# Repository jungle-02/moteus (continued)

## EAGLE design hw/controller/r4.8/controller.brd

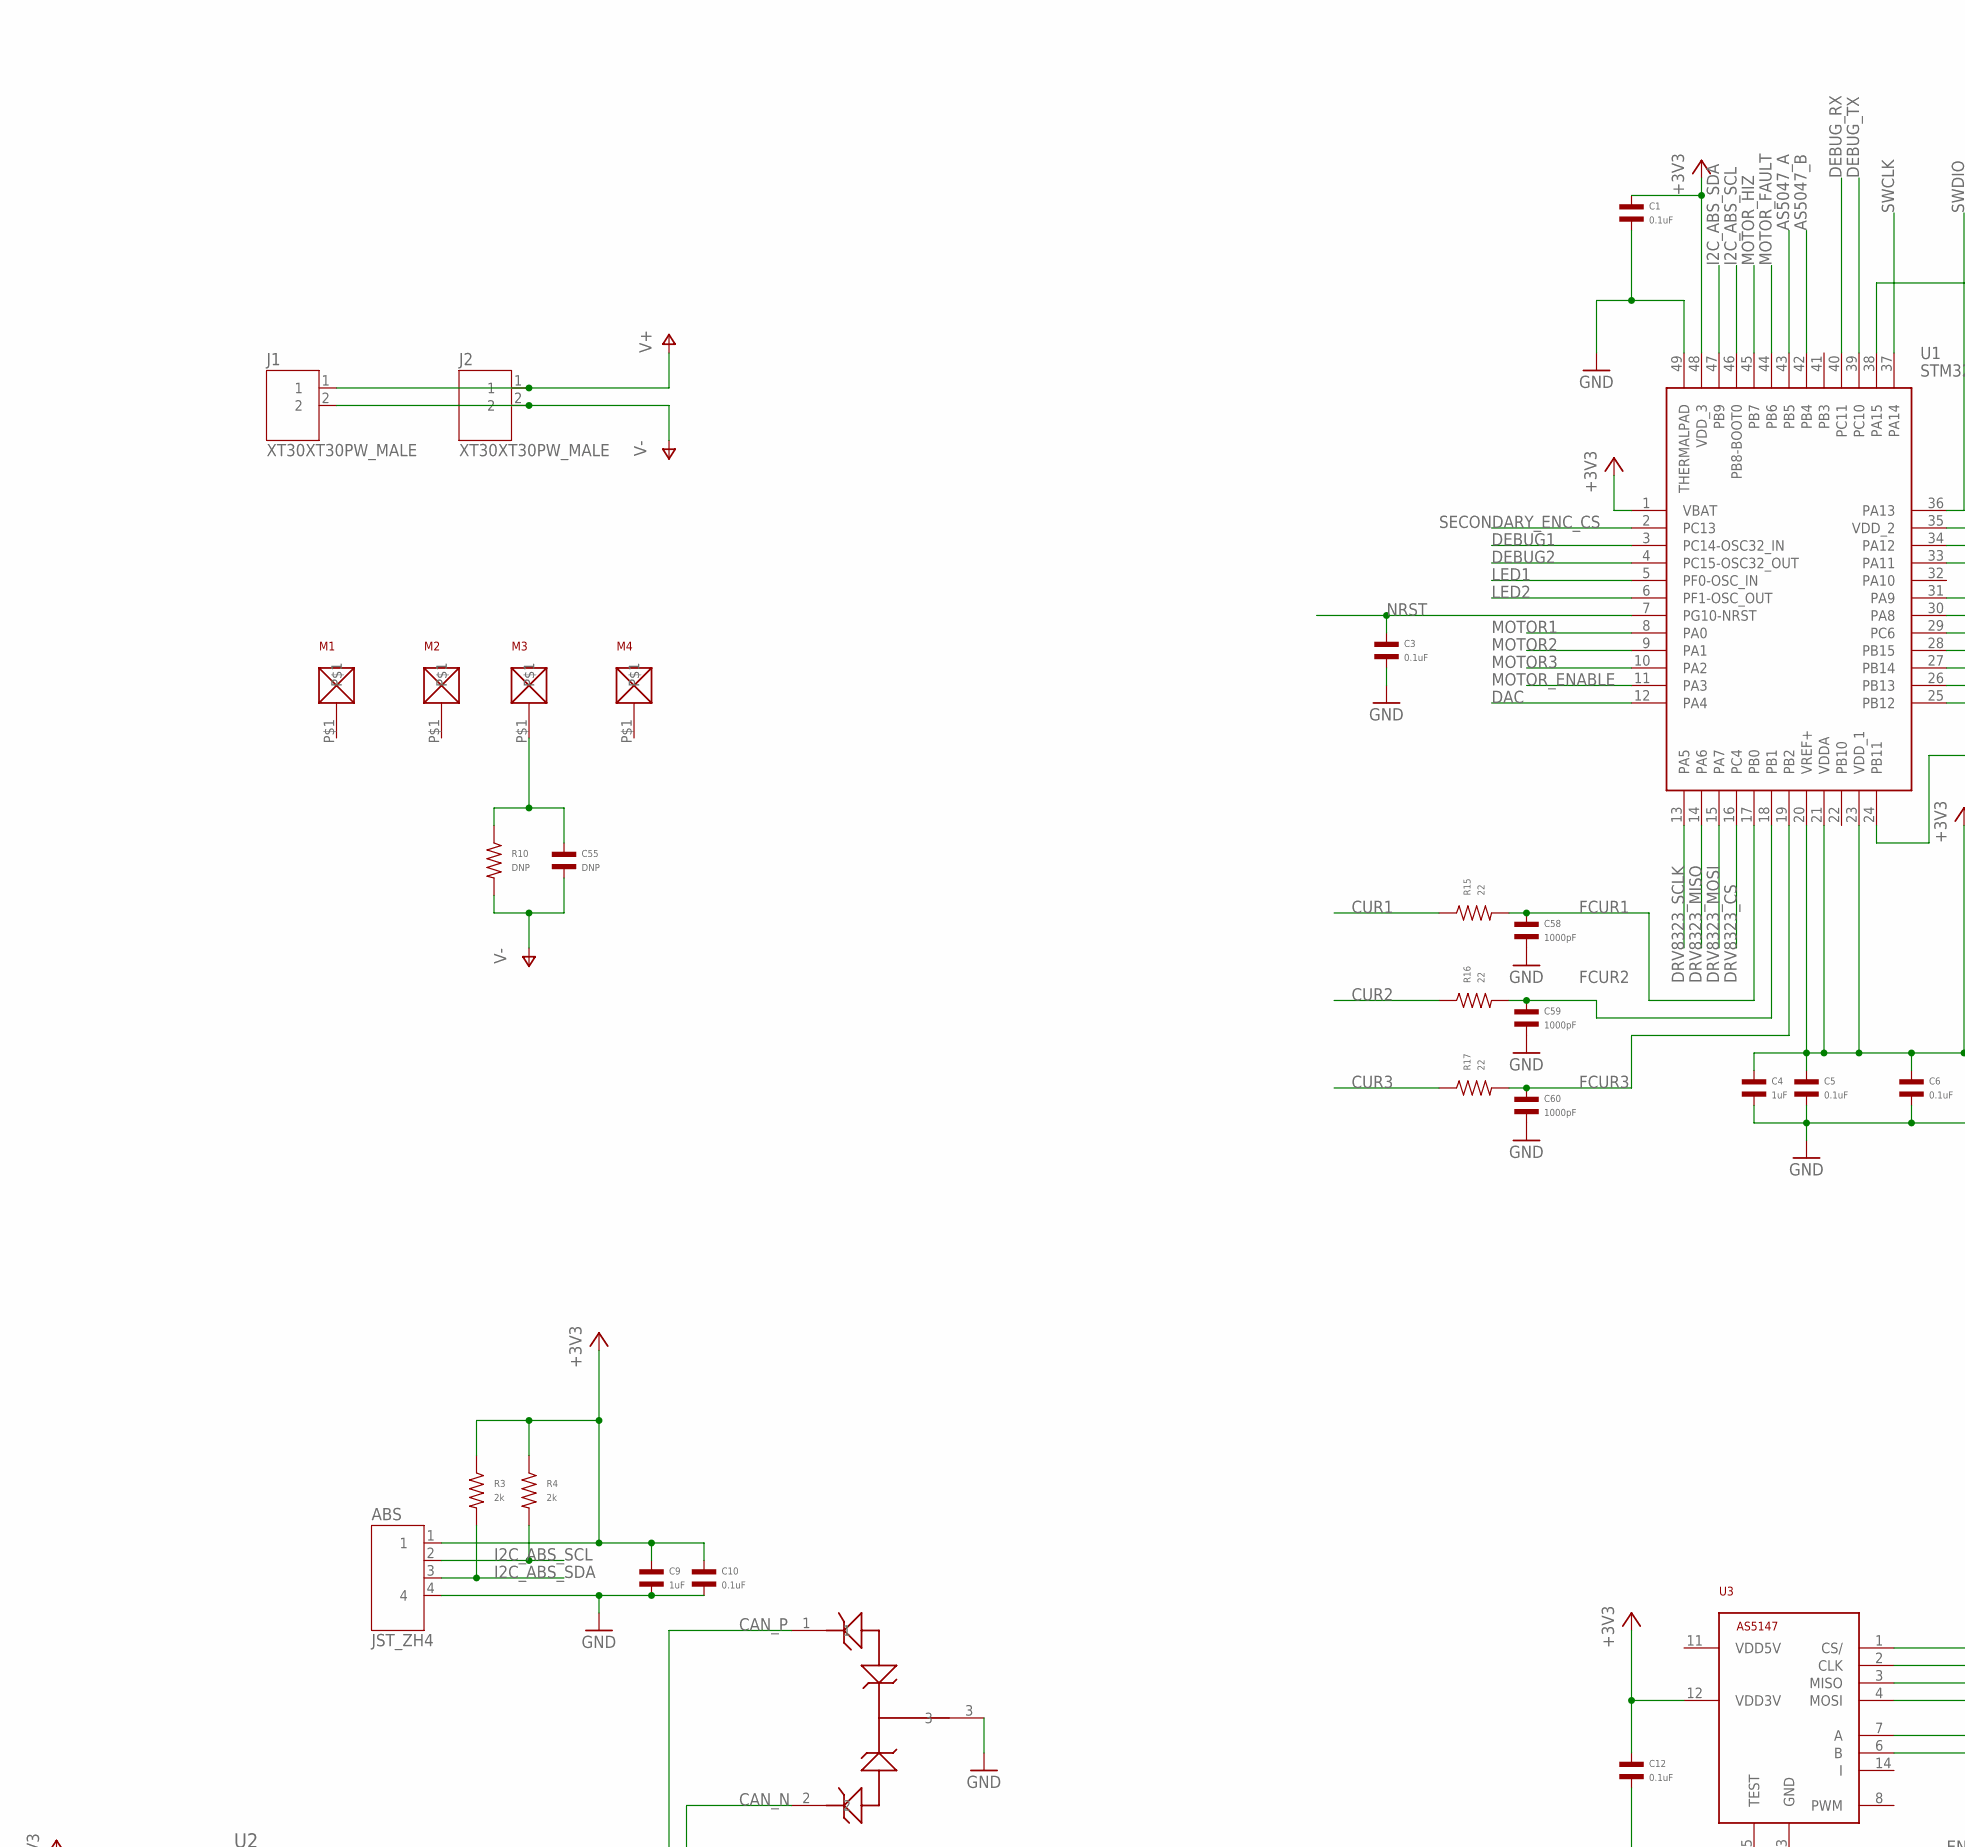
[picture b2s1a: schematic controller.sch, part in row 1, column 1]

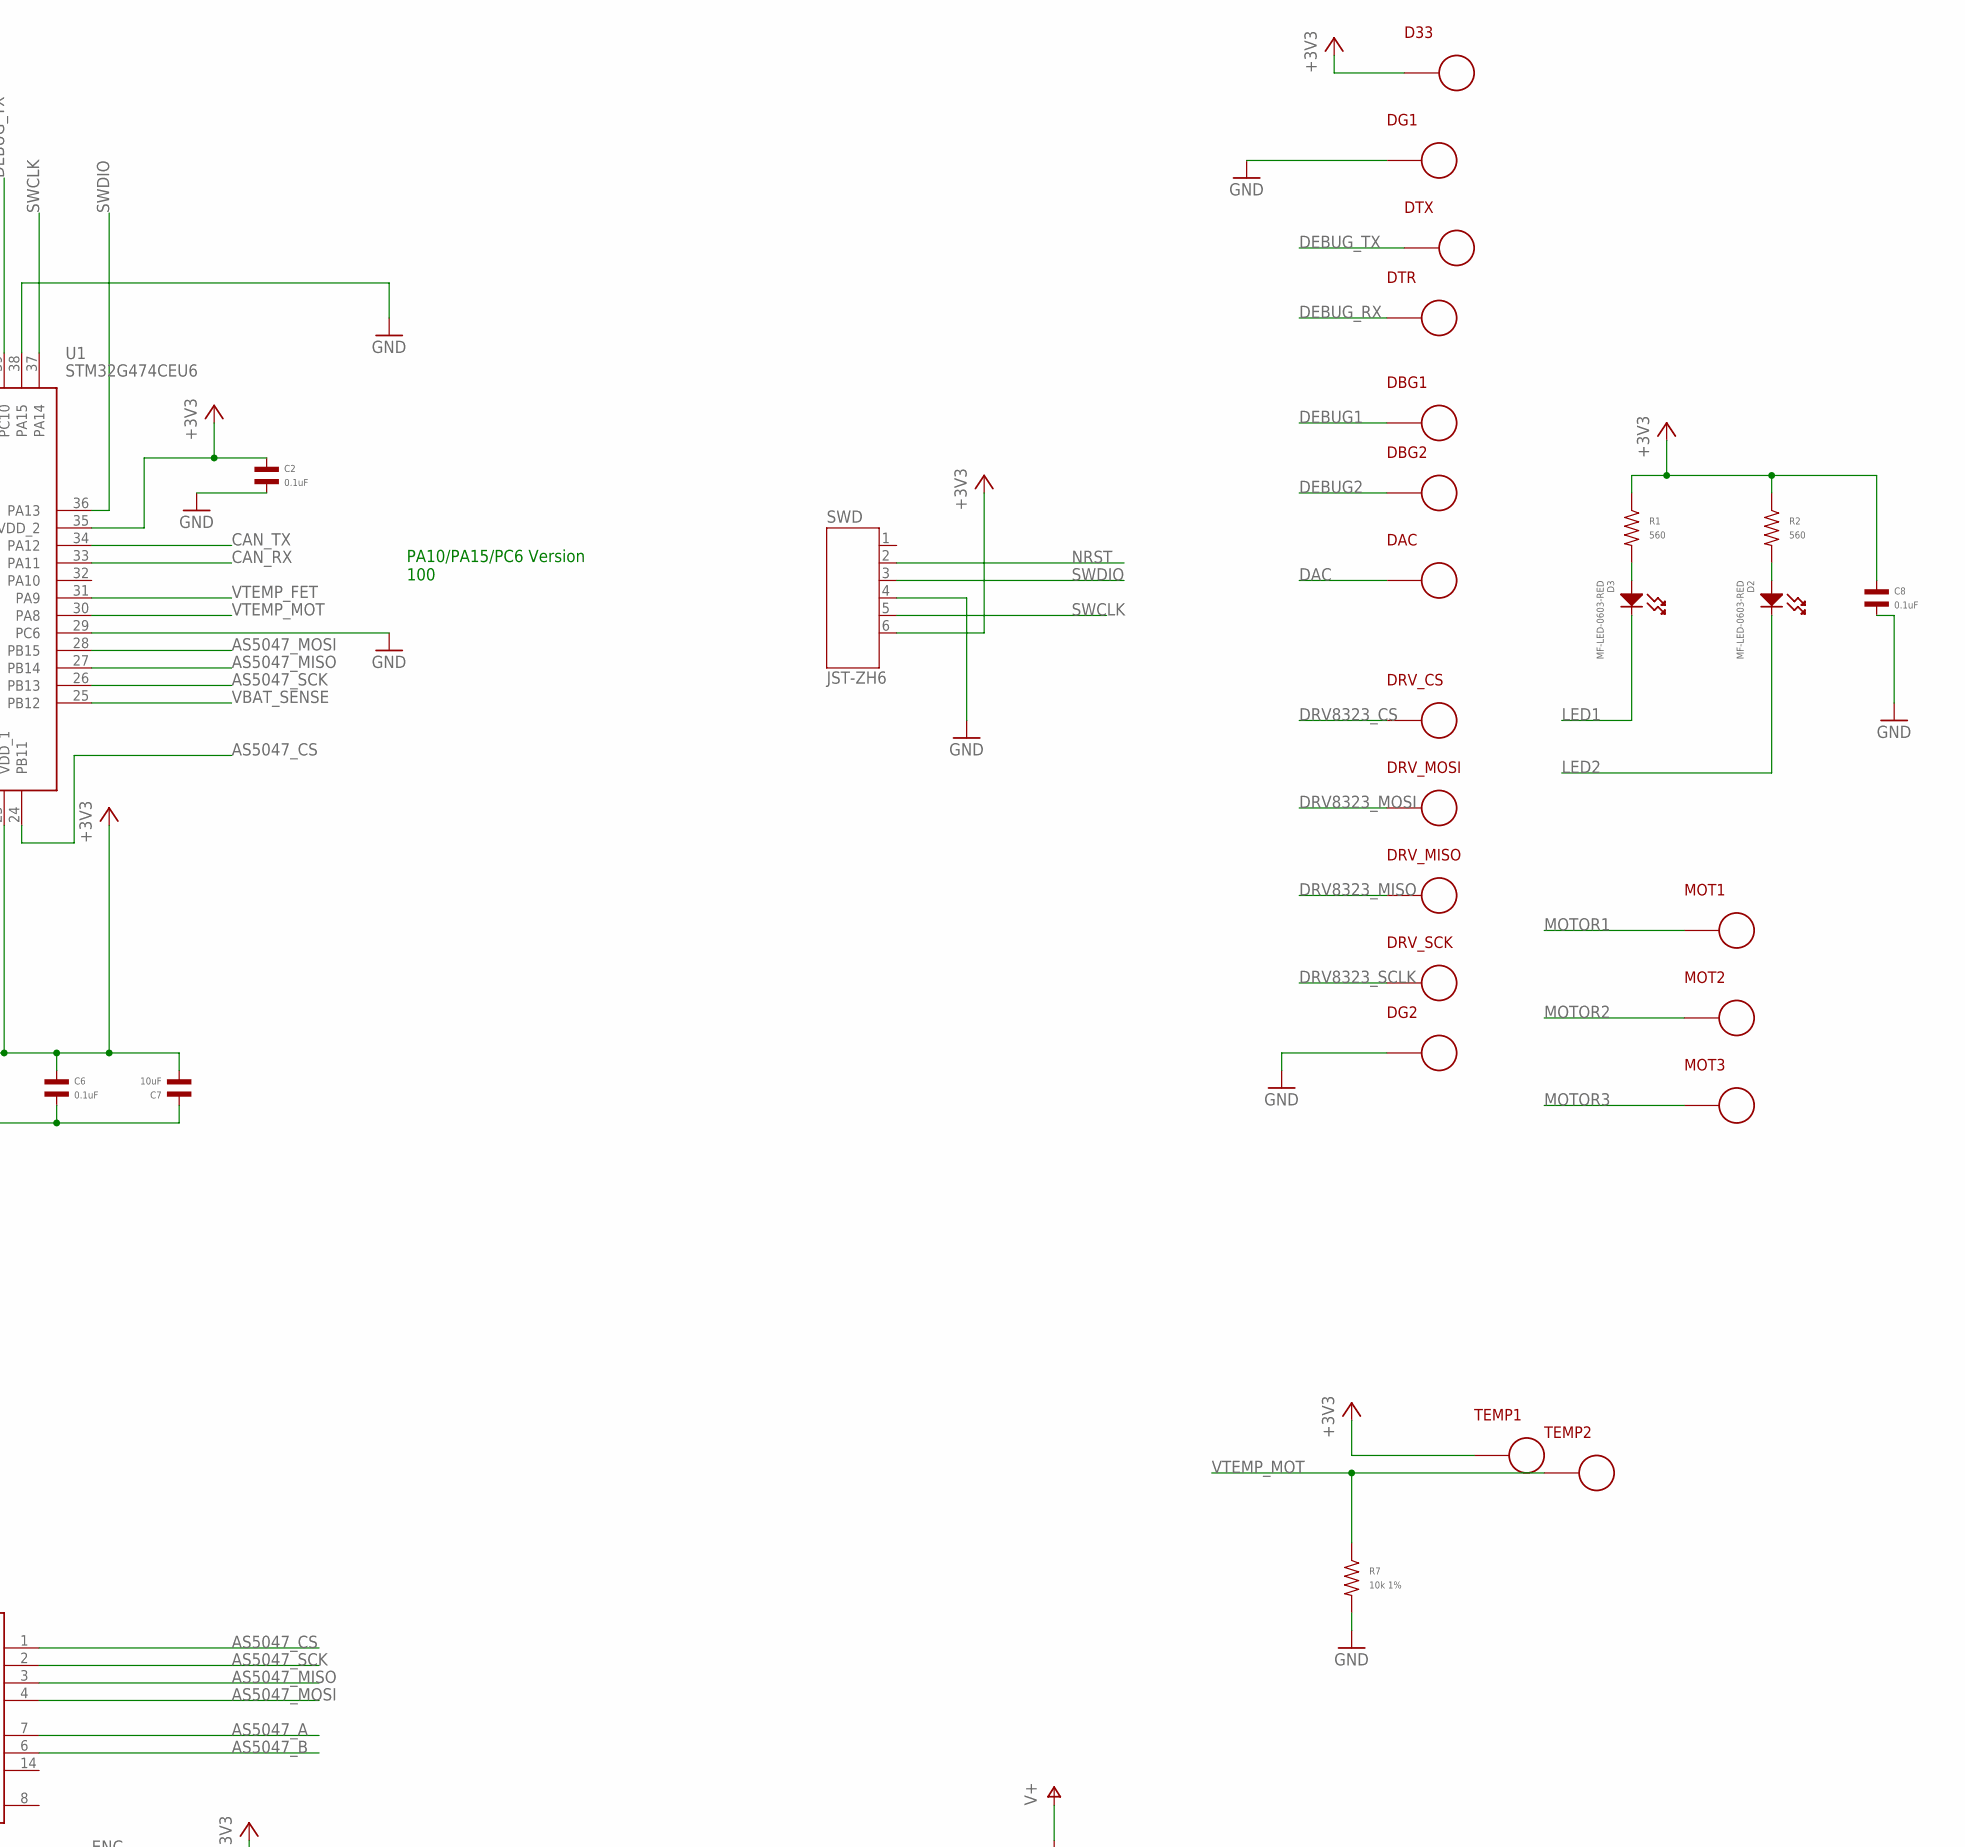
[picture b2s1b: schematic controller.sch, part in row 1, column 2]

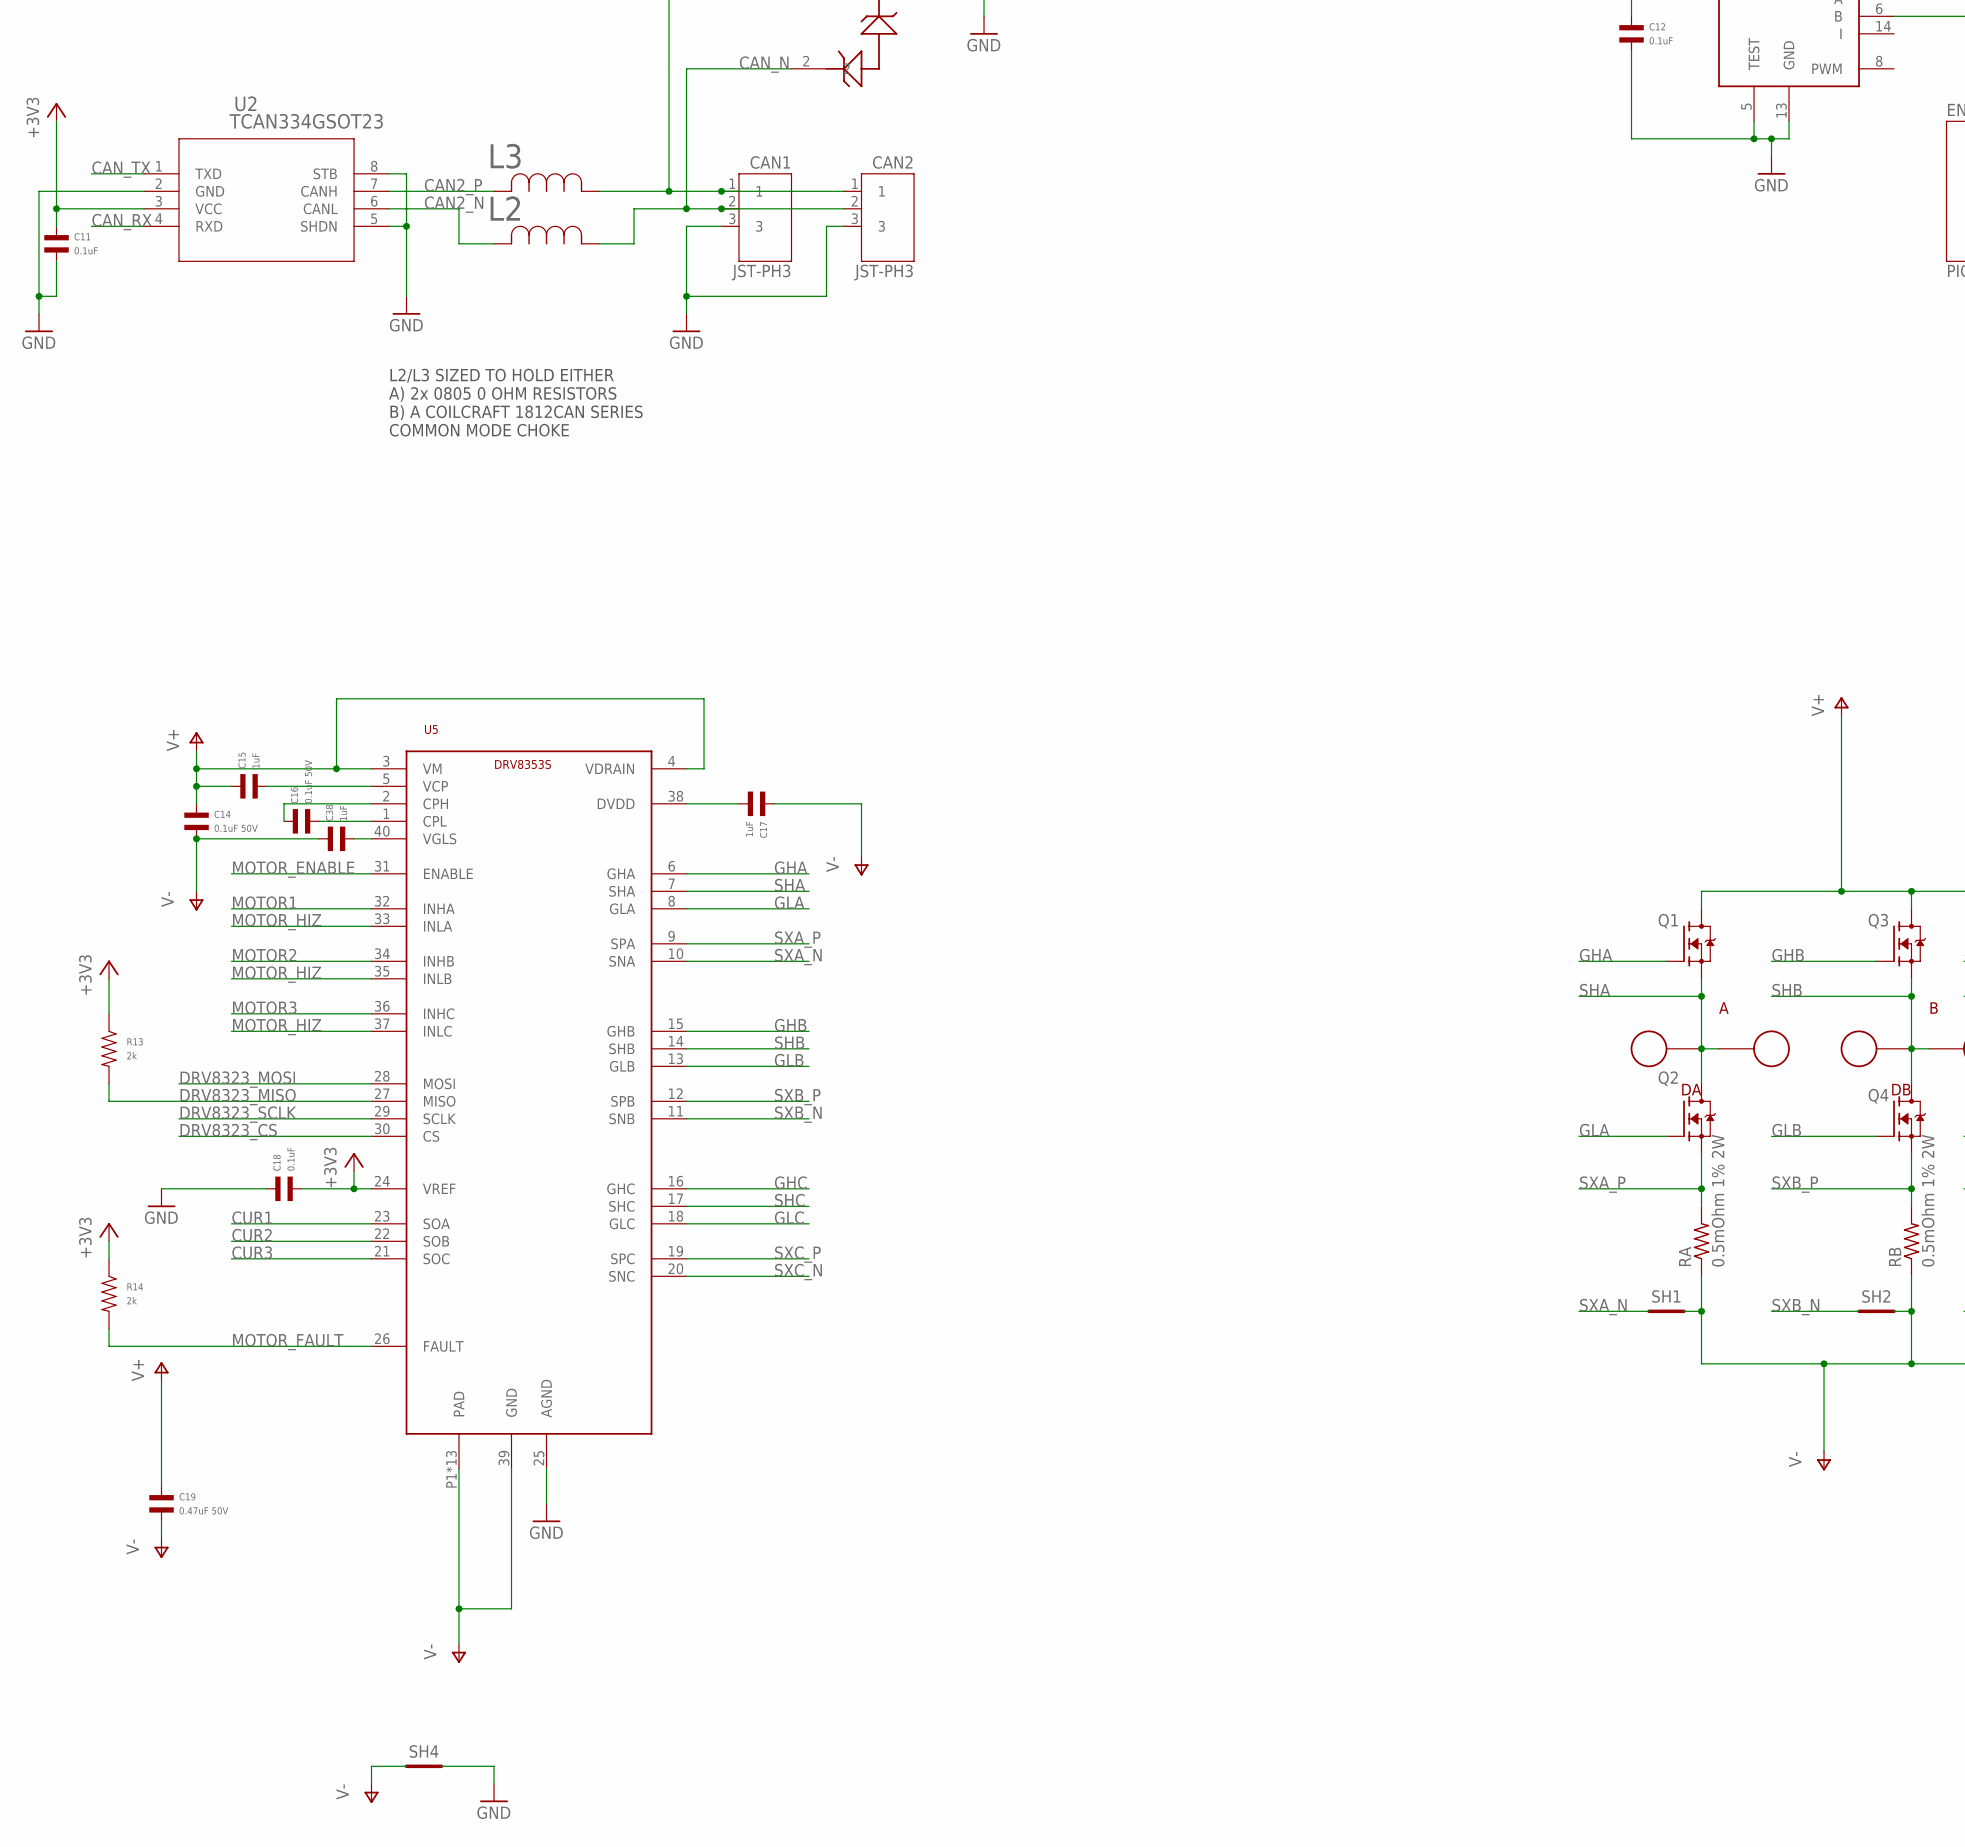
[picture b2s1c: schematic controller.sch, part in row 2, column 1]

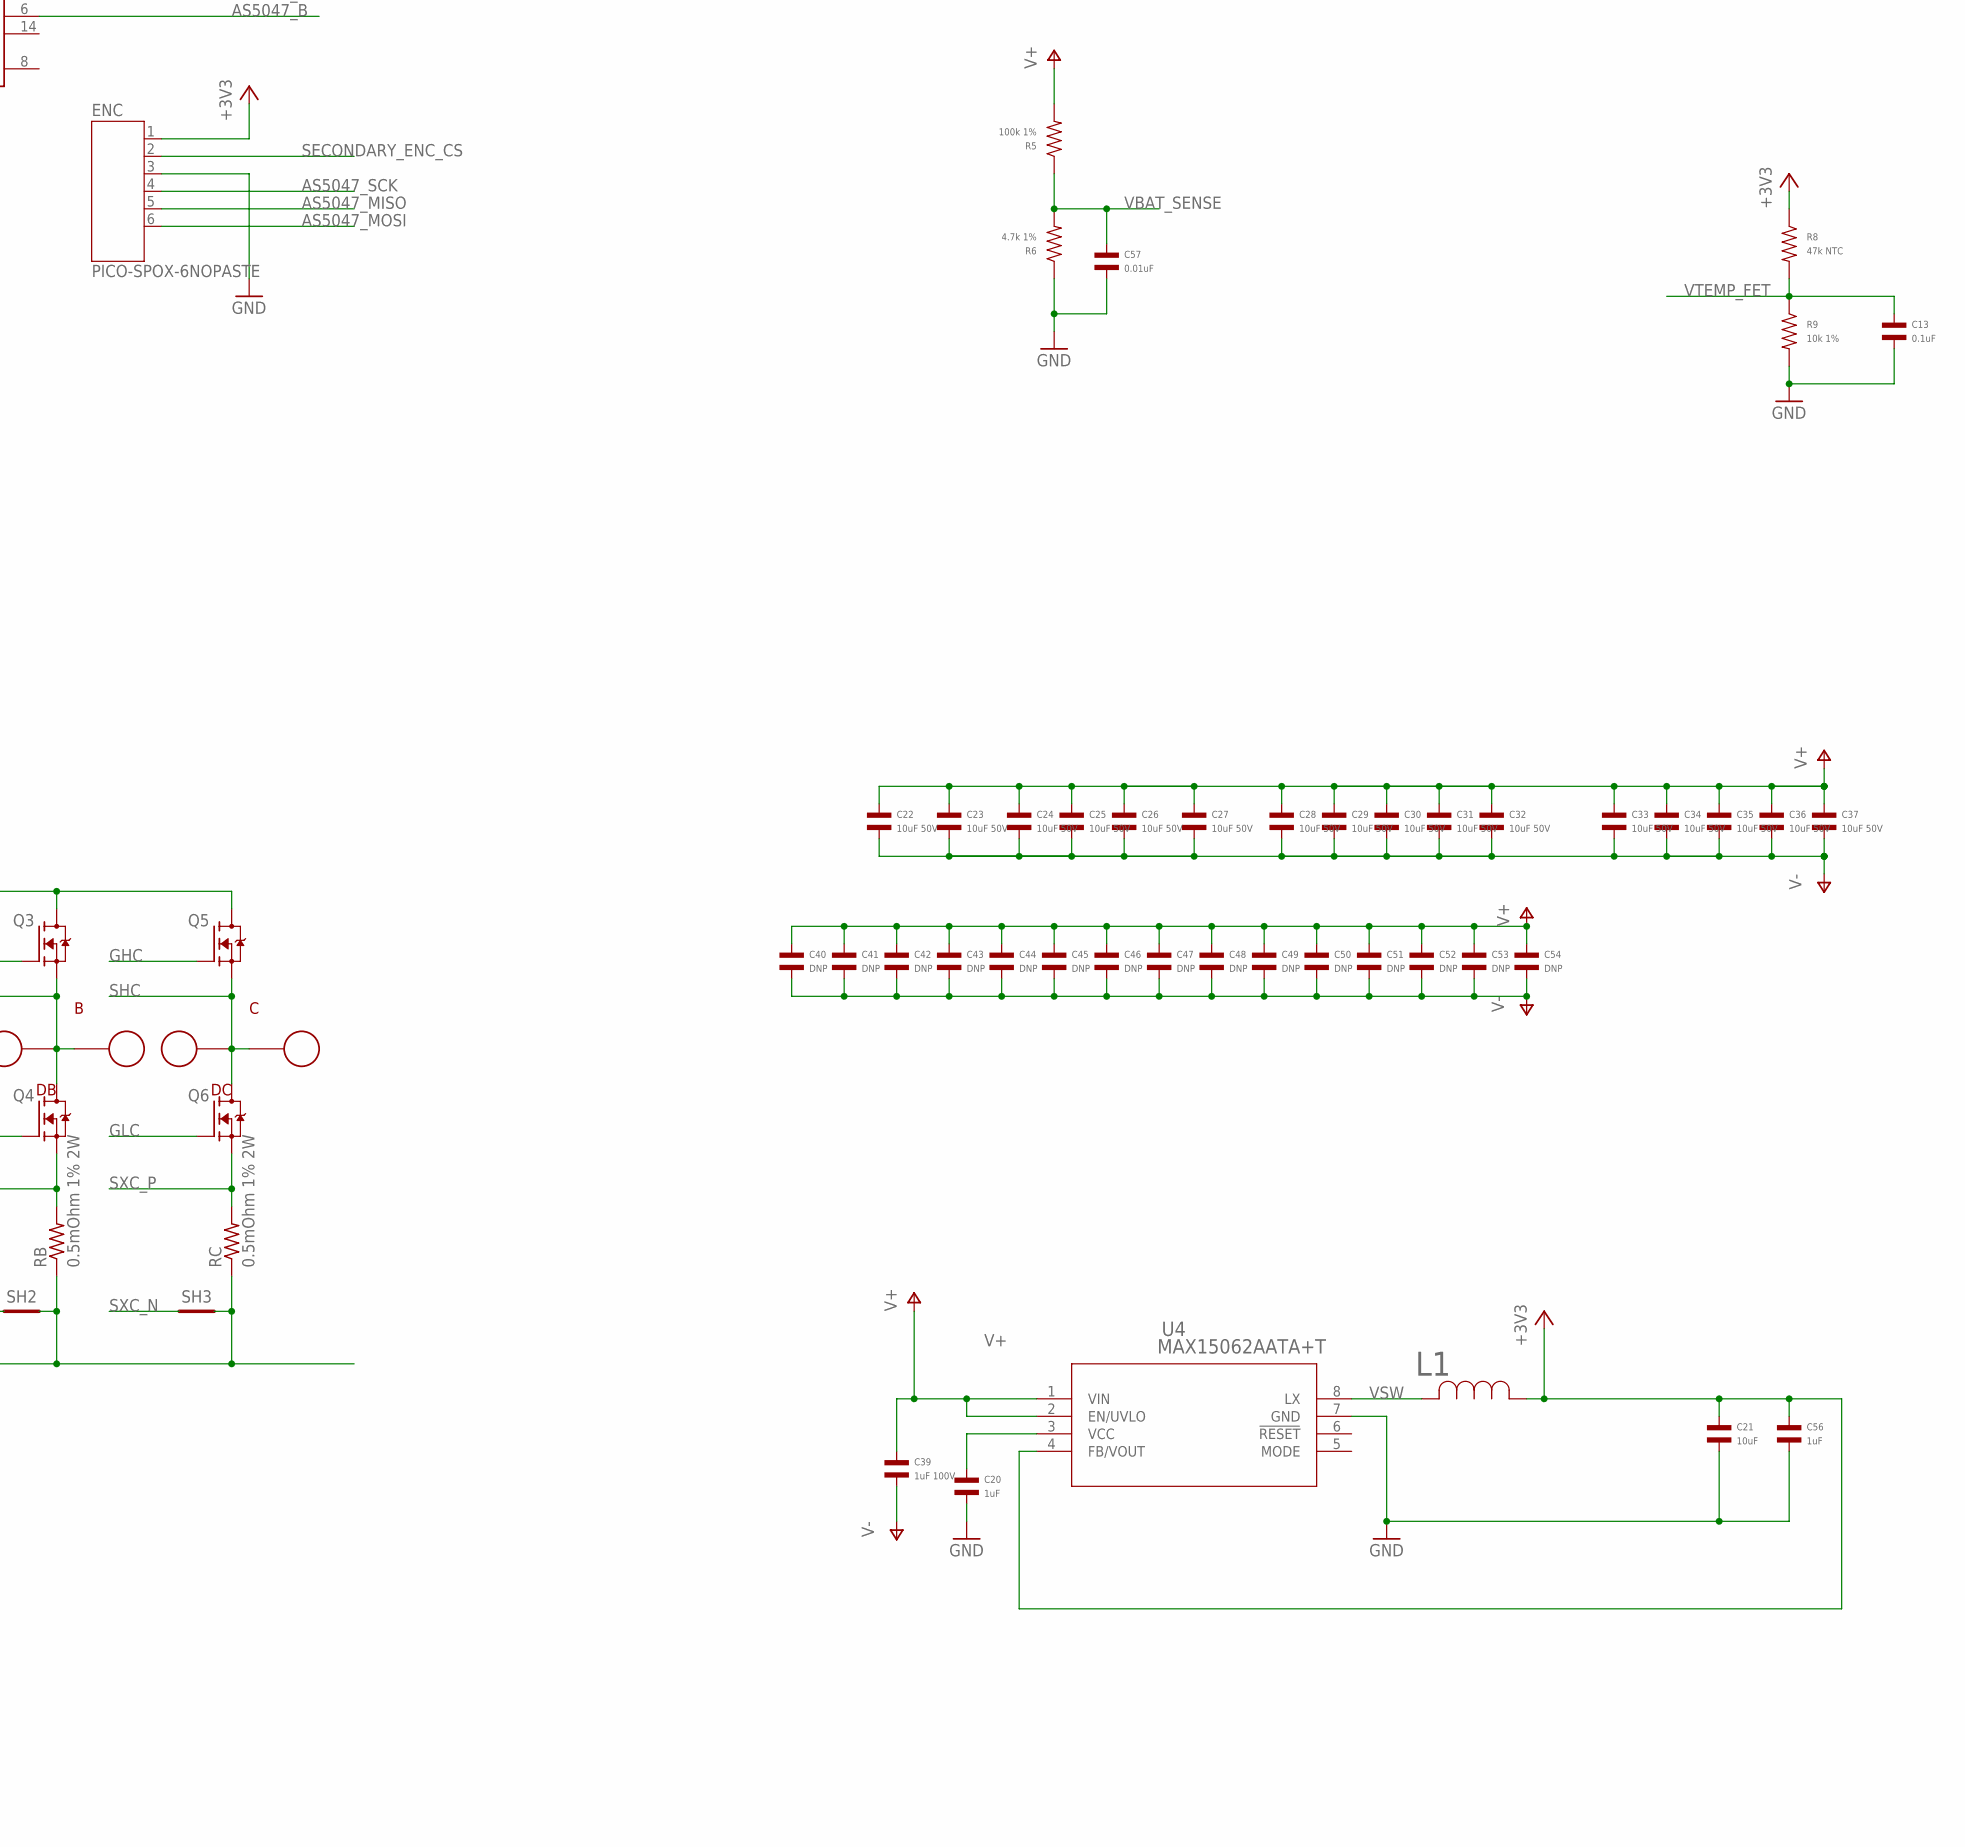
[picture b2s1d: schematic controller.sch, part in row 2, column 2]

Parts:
A: PAD16AWG_PAD; 16AWG_PAD
ABS: JST_ZH4; JST_S4B-ZR-SM4A-TF(LF)(SN); MPN S4B-ZR-SM4A-TF(LF)(SN)
B: PAD16AWG_PAD; 16AWG_PAD
C: PAD16AWG_PAD; 16AWG_PAD
C1, C2, C3, C5, C6, C8, C10, C11, C12, C13, C18: 0.1uF; C0402; MPN MF-CAP-0402-0.1uF
C4, C9, C15, C17, C38, C56: 1uF; C0402; MPN MF-CAP-0402-1uF
C7, C21: 10uF; C1206; MPN MF-CAP-1206-10uF
C14, C16: 0.1uF 50V; C0402; MPN CGA2B3X7R1H104K050BB
C19: 0.47uF 50V; C0402; MPN GRM155R61H474KE11D
C20: 1uF; C0603; MPN MF-CAP-0603-1uF
C22, C23, C24, C25, C26, C27, C28, C29, C30, C31, C32, C33, C34, C36, C37: 10uF 50V; C1206; MPN C3216X7R1H106K160AE
C35: 10uF 50V; C1206_NOBORDER; MPN C3216X7R1H106K160AE
C39: 1uF 100V; C0805; MPN GCM21BC72A105KE36L
C40, C41, C42, C43, C44, C45, C46, C47, C48, C49, C50, C51, C52, C53, C54: DNP; C1206_NOCREAM
C55: DNP; C0402
C57: 0.01uF; C0402; MPN MF-CAP-0402-0.01uF
C58, C59, C60: 1000pF; C0402; MPN MF-CAP-0402-1nF
CAN1, CAN2: JST-PH3; JST_S3B-PH-SM4-TB(LF)(SN); MPN S3B-PH-SM4-TB(LF)(SN)
D2: MF-LED-0603-RED; LED0603; MPN MF-LED-0603-GREEN
D3: MF-LED-0603-RED; LED0603
D4: DUAL_TVS; SOT23-3; MPN CDSOT23-0502B
D33: PAD24AWG_PAD; 24AWG_PAD
DA: PAD24AWG_PAD; 24AWG_PAD
DAC: PAD24AWG_PAD; 24AWG_PAD
DB: PAD24AWG_PAD; 24AWG_PAD
DBG1, DBG2: PAD24AWG_PAD; 24AWG_PAD
DC: PAD24AWG_PAD; 24AWG_PAD
DG1, DG2: PAD24AWG_PAD; 24AWG_PAD
DRV_CS: PAD24AWG_PAD; 24AWG_PAD
DRV_MISO: PAD24AWG_PAD; 24AWG_PAD
DRV_MOSI: PAD24AWG_PAD; 24AWG_PAD
DRV_SCK: PAD24AWG_PAD; 24AWG_PAD
DTR: PAD24AWG_PAD; 24AWG_PAD
DTX: PAD24AWG_PAD; 24AWG_PAD
ENC: PICO-SPOX-6NOPASTE; PICO-SPOX-SMT-RA-6-NOPASTE
J1, J2: XT30XT30PW_MALE; XT30PW_MALE
L1: SRN4018-220M; IND_BOURNS_SRN4018; MANUFACTURER_PART_NUMBER SRN4018-330M
L2, L3: HALF_CHOKE; 1812_COMMON_HALF; MPN MF-RES-0805-0
M1, M2, M3, M4: MOUNT; M2.5MOUNT
MOT1, MOT2, MOT3: PAD24AWG_PAD; 24AWG_PAD
Q1, Q2, Q3, Q4, Q5, Q6: TPH1R204PLSOP_ADVANCE_8; SOP_ADVANCE_8; MPN TPH2R506PL,L1Q
R1, R2: 560; R0402; MPN MF-RES-0402-560
R3, R4, R13, R14: 2k; R0402; MPN MF-RES-0402-2K
R5: 100k 1%; R0402; MPN RC0402FR-07100KL
R6: 4.7k 1%; R0402; MPN RC0402FR-074K7L
R7, R9: 10k 1%; R0402; MPN RC0402FR-0710KL
R8: 47k NTC; R0402; MPN NCP15WB473F03RC
R10: DNP; R0402
R15, R16, R17: 22; R0402; MPN MF-RES-0402-22
RA: 0.5mOhm 1% 2W; M1206; MPN HCS1206FTL500
RB: 0.5mOhm 1% 2W; M1206; MPN HCS1206FTL500
RC: 0.5mOhm 1% 2W; M1206; MPN HCS1206FTL500
SH1, SH2, SH3: SHORTT5; SHORT_TOP-50
SH4: SHORTMEDIUM; SHORT_TOP-MEDIUM
SWD: JST-ZH6; JST_S6B-ZR-SM4A-TF(LF)(SN); MPN S6B-ZR-SM4A-TF(LF)(SN)
TEMP1, TEMP2: PAD24AWG_PAD; 24AWG_PAD
U1: STM32G474CEU6; QFN50P700X700X60-49N; MPN STM32G474CEU6
U2: TCAN334GSOT23; SOT23-8; MPN TCAN334GDCNT
U3: AS5147; TSSOP14; MPN AS5047P-ATSM
U4: MAX15062AATA+T; 21-0487A_MXM; MPN MAX15062AATA+T
U5: DRV8353S; WQFN-40; MPN DRV8353FSRTAR

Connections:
+3V3: ABS.1, C1.P$1, C2.P$1, C4.P$1, C5.P$1, C6.P$1, C7.P$2, C8.P$1, C9.P$1, C10.P$1, C11.P$1, C12.P$1, C18.P$2, C21.P$1, C56.P$1, D33.P$1, ENC.1, L1.1, R1.P$1, R2.P$1, R3.P$1, R4.P$1, R8.P$1, R13.P$1, R14.P$1, SWD.6, TEMP1.P$1, U1.1 (VBAT), U1.20 (VREF+), U1.21 (VDDA), U1.23 (VDD_1), U1.35 (VDD_2), U1.48 (VDD_3), U2.3 (VCC), U3.12 (VDD3V), U4.4 (FB/VOUT), U5.24 (VREF)
AS5047_A: U1.43 (PB5), U3.7 (A)
AS5047_B: U1.42 (PB4), U3.6 (B)
AS5047_CS: U1.24 (PB11), U3.1 (CS/)
AS5047_MISO: ENC.5, U1.27 (PB14), U3.3 (MISO)
AS5047_MOSI: ENC.6, U1.28 (PB15), U3.4 (MOSI)
AS5047_SCK: ENC.4, U1.26 (PB13), U3.2 (CLK)
CAN2_N: L2.P$2 (2), U2.6 (CANL)
CAN2_P: L3.P$2 (2), U2.7 (CANH)
CAN_N: CAN1.2, CAN2.2, D4.2, L2.P$1 (1)
CAN_P: CAN1.1, CAN2.1, D4.1, L3.P$1 (1)
CAN_RX: U1.33 (PA11), U2.4 (RXD)
CAN_TX: U1.34 (PA12), U2.1 (TXD)
CUR1: R15.P$1, U5.23 (SOA)
CUR2: R16.P$1, U5.22 (SOB)
CUR3: R17.P$1, U5.21 (SOC)
DAC: DAC.P$1, U1.12 (PA4)
DEBUG1: DBG1.P$1, U1.3 (PC14-OSC32_IN)
DEBUG2: DBG2.P$1, U1.4 (PC15-OSC32_OUT)
DEBUG_RX: DTR.P$1, U1.40 (PC11)
DEBUG_TX: DTX.P$1, U1.39 (PC10)
DRV8323_CS: DRV_CS.P$1, U1.16 (PC4), U5.30 (CS)
DRV8323_MISO: DRV_MISO.P$1, R13.P$2, U1.14 (PA6), U5.27 (MISO)
DRV8323_MOSI: DRV_MOSI.P$1, U1.15 (PA7), U5.28 (MOSI)
DRV8323_SCLK: DRV_SCK.P$1, U1.13 (PA5), U5.29 (SCLK)
FCUR1: C58.P$1, R15.P$2, U1.17 (PB0)
FCUR2: C59.P$1, R16.P$2, U1.18 (PB1)
FCUR3: C60.P$1, R17.P$2, U1.19 (PB2)
GHA: Q1.4 (G), U5.6 (GHA)
GHB: Q3.4 (G), U5.15 (GHB)
GHC: Q5.4 (G), U5.16 (GHC)
GLA: Q2.4 (G), U5.8 (GLA)
GLB: Q4.4 (G), U5.13 (GLB)
GLC: Q6.4 (G), U5.18 (GLC)
GND: ABS.4, C1.P$2, C2.P$2, C3.P$2, C4.P$2, C5.P$2, C6.P$2, C7.P$1, C8.P$2, C9.P$2, C10.P$2, C11.P$2, C12.P$2, C13.P$2, C18.P$1, C20.P$2, C21.P$2, C56.P$2, C57.P$2, C58.P$2, C59.P$2, C60.P$2, CAN1.3, CAN2.3, D4.3, DG1.P$1, DG2.P$1, ENC.3, R6.P$1, R7.P$2, R9.P$2, SH4.2, SWD.4, U1.29 (PC6), U1.38 (PA15), U1.49 (THERMALPAD), U2.2 (GND), U2.5 (SHDN), U2.8 (STB), U3.5 (TEST), U3.13 (GND), U4.7 (GND), U5.25 (AGND)
I2C_ABS_SCL: ABS.2, R4.P$2, U1.46 (PB8-BOOT0)
I2C_ABS_SDA: ABS.3, R3.P$2, U1.47 (PB9)
LED1: D3.CATHODE, U1.5 (PF0-OSC_IN)
LED2: D2.CATHODE, U1.6 (PF1-OSC_OUT)
MOTOR1: MOT1.P$1, U1.8 (PA0), U5.32 (INHA)
MOTOR2: MOT2.P$1, U1.9 (PA1), U5.34 (INHB)
MOTOR3: MOT3.P$1, U1.10 (PA2), U5.36 (INHC)
MOTOR_ENABLE: U1.11 (PA3), U5.31 (ENABLE)
MOTOR_FAULT: R14.P$2, U1.44 (PB6), U5.26 (FAULT)
MOTOR_HIZ: U1.45 (PB7), U5.33 (INLA), U5.35 (INLB), U5.37 (INLC)
unnamed: C55.P$1, M3.P$1, R10.P$1
unnamed: C38.P$2, U5.40 (VGLS)
unnamed: C20.P$1, U4.3 (VCC)
unnamed: C16.P$2, U5.1 (CPL)
unnamed: C16.P$1, U5.2 (CPH)
unnamed: C15.P$2, U5.5 (VCP)
unnamed: C17.P$2, U5.38 (DVDD)
unnamed: D3.ANODE, R1.P$2
unnamed: D2.ANODE, R2.P$2
NRST: C3.P$1, SWD.2, U1.7 (PG10-NRST)
SECONDARY_ENC_CS: ENC.2, U1.2 (PC13)
SHA: A.1, DA.P$1, Q1.1 (S), Q1.2 (S), Q1.3 (S), Q2.5 (D), Q2.6 (D), Q2.7 (D), Q2.8 (D), Q2.PAD (D), U5.7 (SHA)
SHB: B.1, DB.P$1, Q3.1 (S), Q3.2 (S), Q3.3 (S), Q4.5 (D), Q4.6 (D), Q4.7 (D), Q4.8 (D), Q4.PAD (D), U5.14 (SHB)
SHC: C.1, DC.P$1, Q5.1 (S), Q5.2 (S), Q5.3 (S), Q6.5 (D), Q6.6 (D), Q6.7 (D), Q6.8 (D), Q6.PAD (D), U5.17 (SHC)
SWCLK: SWD.5, U1.37 (PA14)
SWDIO: SWD.3, U1.36 (PA13)
SXA_N: SH1.1, U5.10 (SNA)
SXA_P: Q2.1 (S), Q2.2 (S), Q2.3 (S), RA.2, U5.9 (SPA)
SXB_N: SH2.1, U5.11 (SNB)
SXB_P: Q4.1 (S), Q4.2 (S), Q4.3 (S), RB.2, U5.12 (SPB)
SXC_N: SH3.1, U5.20 (SNC)
SXC_P: Q6.1 (S), Q6.2 (S), Q6.3 (S), RC.2, U5.19 (SPC)
V+: C14.P$1, C15.P$1, C19.P$1, C22.P$1, C23.P$1, C24.P$1, C25.P$1, C26.P$1, C27.P$1, C28.P$1, C29.P$1, C30.P$1, C31.P$1, C32.P$1, C33.P$1, C34.P$1, C35.P$1, C36.P$1, C37.P$1, C39.P$1, C40.P$1, C41.P$1, C42.P$1, C43.P$1, C44.P$1, C45.P$1, C46.P$1, C47.P$1, C48.P$1, C49.P$1, C50.P$1, C51.P$1, C52.P$1, C53.P$1, C54.P$1, J1.1, J2.1, Q1.5 (D), Q1.6 (D), Q1.7 (D), Q1.8 (D), Q1.PAD (D), Q3.5 (D), Q3.6 (D), Q3.7 (D), Q3.8 (D), Q3.PAD (D), Q5.5 (D), Q5.6 (D), Q5.7 (D), Q5.8 (D), Q5.PAD (D), R5.P$2, U4.1 (VIN), U4.2 (EN/UVLO), U5.3 (VM), U5.4 (VDRAIN)
V-: C14.P$2, C17.P$1, C19.P$2, C22.P$2, C23.P$2, C24.P$2, C25.P$2, C26.P$2, C27.P$2, C28.P$2, C29.P$2, C30.P$2, C31.P$2, C32.P$2, C33.P$2, C34.P$2, C35.P$2, C36.P$2, C37.P$2, C38.P$1, C39.P$2, C40.P$2, C41.P$2, C42.P$2, C43.P$2, C44.P$2, C45.P$2, C46.P$2, C47.P$2, C48.P$2, C49.P$2, C50.P$2, C51.P$2, C52.P$2, C53.P$2, C54.P$2, C55.P$2, J1.2, J2.2, R10.P$2, RA.1, RB.1, RC.1, SH1.2, SH2.2, SH3.2, SH4.1, U5.39 (GND), U5.P1 (PAD), U5.P2 (PAD), U5.P3 (PAD), U5.P7 (PAD), U5.P8 (PAD), U5.P9 (PAD), U5.P12 (PAD), U5.P13 (PAD), U5.P14 (PAD), U5.P17 (PAD), U5.P18 (PAD), U5.P19 (PAD), U5.PAD
VBAT_SENSE: C57.P$1, R5.P$1, R6.P$2, U1.25 (PB12)
VSW: L1.2, U4.8 (LX)
VTEMP_FET: C13.P$1, R8.P$2, R9.P$1, U1.31 (PA9)
VTEMP_MOT: R7.P$1, TEMP2.P$1, U1.30 (PA8)

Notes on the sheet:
PA10/PA15/PC6 Version 100
L2/L3 SIZED TO HOLD EITHER A) 2x 0805 0 OHM RESISTORS B) A COILCRAFT 1812CAN SERIES COMMON MODE CHOKE

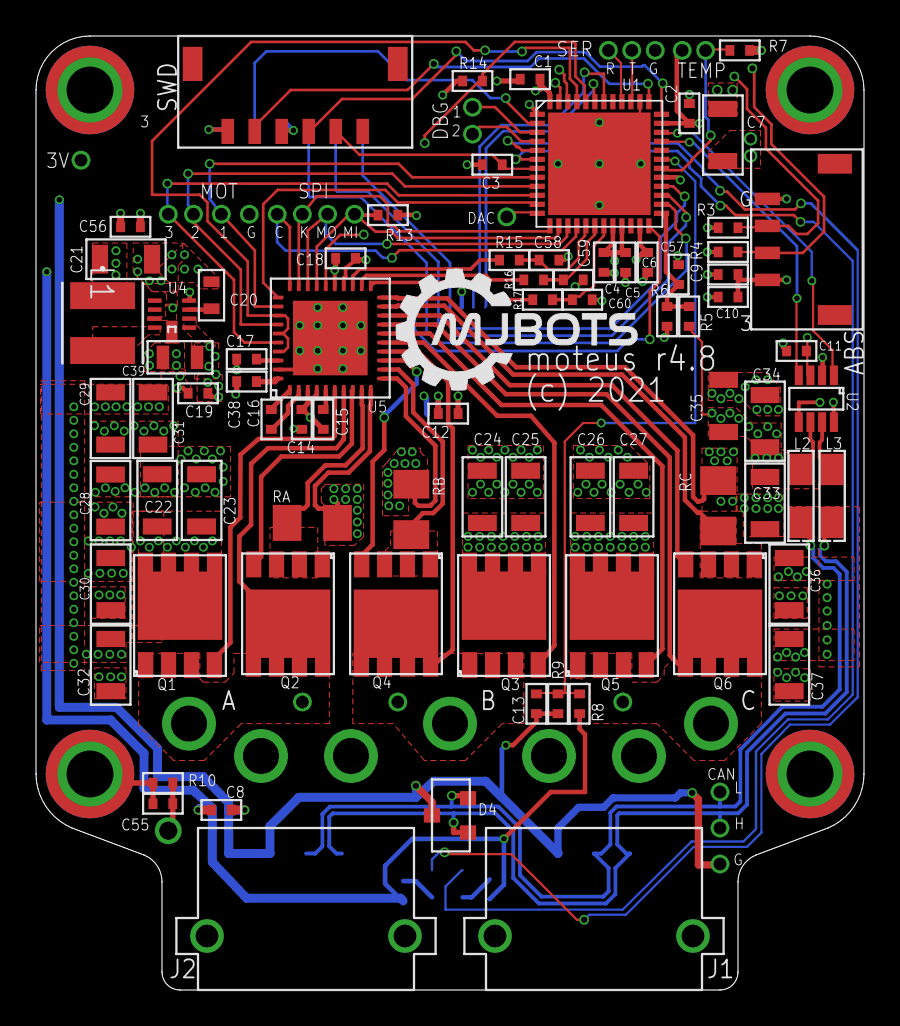
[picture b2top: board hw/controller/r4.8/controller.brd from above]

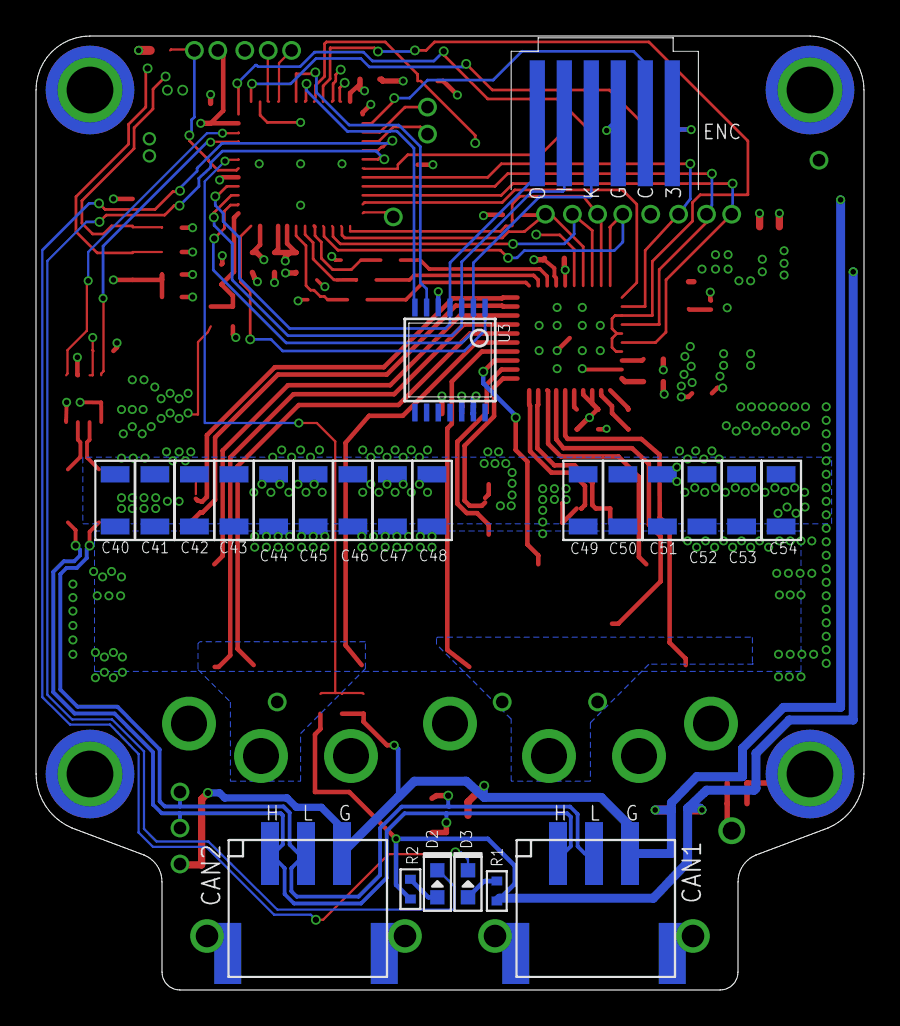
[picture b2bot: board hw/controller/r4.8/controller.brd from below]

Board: 4 copper layers, 46.0 x 53.0 mm, 133 parts (23 on the bottom side), 73 nets.

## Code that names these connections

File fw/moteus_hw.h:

// Copyright 2023 mjbots Robotic Systems, LLC.  info@mjbots.com
//
// Licensed under the Apache License, Version 2.0 (the "License");
// you may not use this file except in compliance with the License.
// You may obtain a copy of the License at
//
//     http://www.apache.org/licenses/LICENSE-2.0
//
// Unless required by applicable law or agreed to in writing, software
// distributed under the License is distributed on an "AS IS" BASIS,
// WITHOUT WARRANTIES OR CONDITIONS OF ANY KIND, either express or implied.
// See the License for the specific language governing permissions and
// limitations under the License.

#pragma once

#include "mbed.h"

#include "fw/millisecond_timer.h"

namespace moteus {

//////////////////////////////////////////
// The following "families" are supported:
//  moteus    - family 0
//  moteus-n1 - family 1
//  moteus-c1 - family 2
//
// Each family has an independent hardware version timeline, and
// possibly a different mechanism for verifying hardware version
// compatibility.


// This structure is filled in once the family and hardware version
// are known.
struct MoteusHwPins {
  PinName pwm1 = PA_0_ALT0;
  PinName pwm2 = PA_1_ALT0;
  PinName pwm3 = PA_2_ALT0;

  PinName drv8323_enable = NC;
  PinName drv8323_hiz = NC;
  PinName drv8323_cs = NC;

  PinName drv8323_mosi = NC;
  PinName drv8323_miso = NC;
  PinName drv8323_sck = NC;
  PinName drv8323_fault = NC;

  PinName debug_led1 = NC;
  PinName power_led = NC;

  PinName current1 = NC;
  PinName current2 = NC;
  PinName current3 = NC;

  PinName vsense = NC;
  PinName tsense = PA_9;

  PinName msense = NC;

  float vsense_adc_scale = 0.0f;

  PinName uart_tx = NC;
  PinName uart_rx = NC;
  PinName uart_dir = NC;

  PinName as5047_cs = NC;

  PinName can_td = NC;
  PinName can_rd = NC;

  PinName debug1 = NC;
  PinName debug2 = NC;
  PinName debug_dac = PA_4;

  uint32_t model_number = 0;

  uint32_t firmware_version = 0x000105;

  // Each board has a power limit curve, below a bus voltage V_l, the
  // P_l power limit is used.  Above bus voltage V_h, P_h power limit
  // is used.  Between, the power limit is linearly interpolated.  All
  // power limits are normalized to 30kHz PWM.
  float power_P_l_W = 0.0f;
  float power_V_l = 24.0f;
  float power_P_h_W = 0.0f;
  float power_V_h = 34.0f;
};


struct FamilyAndVersion {
  int family = 0;
  int hw_version = 0;
  int hw_pins = 0;
};

// Return what family we are executing on.
FamilyAndVersion DetectMoteusFamily(MillisecondTimer*);

MoteusHwPins FindHardwarePins(FamilyAndVersion);


// The "FIRMWARE_VERSION" is a misnomer.  It instead is the equivalent
// of an ABI version, and is incremented when configuration values
// change in a way that would not result in equivalent behavior across
// an upgrade/downgrade.

// Version history:

// # 0x0101 #
//
// * Fixed the calculation of feedforward voltage to have the correct
//   sign for the velocity component.  Previous firmwares,
//   inappropriately applied a negative feedforward term, which
//   counteracted rotation instead of being an actual feedforward.

// # 0x0102 #
//
// * Removed servo.feedforward_scale entirely

// # 0x0103 #
//
// * Added servo.pwm_scale, and for r4.8 boards changed the default
//   value of pwm_comp_off / pwm_comp_mag.

// # 0x0104 #
//
// * Added configurable PWM rates, which changed default values of
//   pwm_comp_mag and pwm_comp_off.

// # 0x0105 #
//
// * Switched to a new encoder and position subsystem.

// # 0x0106 #
//
// * Switched aux?.sources.x.i2c.poll_ms to poll_rate_us to match UART
//   and give more resolution.

// # 0x0107 #
//
// * Fixed motor_position.output.sign == -1 so that DQ commands for
//   voltage or current are inverted, so that positive Q axis voltage
//   or current results in positive speed

// # 0x0108 #
//
// * The default value of `servo.bemf_feedforward` was changed from
//   1.0 to 0.0.

// # 0x0109 #
//
// * Commutation compensation now interpolates, which means old tables
//   need to be upgraded during the flash process.
// * The motor thermistor value is now configurable and defaults to
//   10k instead of 47k.

// # 0x010a #
//
// * servo.max_power_W now defaults to NaN, and if present is used as
//   an absolute value rather than as a "nominal" value.

// # 0x010b #
//
// * servo.flux_brake_margin_voltage replaces
//   servo.flux_brake_min_voltage
// * servo.temperature_margin replaces servo.derate_temperature
// * servo.motor_temperature_margin replaces
//   servo.motor_derate_temperature

// # 0x010c #
//
// * motor_position.sources.x.pll_filter_hz was previously specified
//   in terms of a somewhat arbitrary "natural frequency", but is now
//   specified in terms of the 3dB cutoff frequency

#define MOTEUS_MODEL_NUMBER 0x0000
#define MOTEUS_FIRMWARE_VERSION 0x00010c

extern MoteusHwPins g_hw_pins;

// Ensure the DRV8323 is turned off.
void MoteusEnsureOff();

}
